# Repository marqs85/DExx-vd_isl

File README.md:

DExx-vd_isl
==============

DExx-vd_isl is advanced video digitizer add-on module for a number of Terasic FPGA development boards. It has been initially used as a development board for OSSC Pro scan converter but over time has been tailored towards a standalone product. Please check the [wikipage](https://junkerhq.net/xrgb/index.php?title=DExx-vd_isl) for more information on usage and latest features.

[PCB](pcb/) and firmware of the project are open-source except for certain Intel VIP modules which are planned to be replaced by custom implementations over time. For most parts RTL and SW are derived from OSSC Pro [project](https://github.com/marqs85/ossc_pro/) with only small amount of adaptation code for the supported development boards.

Supported Terasic boards and board specific notes
----------------------------------------------------
* [DE10-Nano](board/de10-nano)
* [C5G](board/c5g)
* [DE2-115](board/de2-115)

Requirements for building and debugging firmware
---------------------------------------------------
* Hardware
  * DExx-vd_isl module and compatible development board

* Software
  * [Altera Quartus Prime + device support files for target FPGA family](http://dl.altera.com/?edition=lite) (v 21.1 or higher - free Lite Edition suffices)
  * Make

Building RTL (bitstream)
--------------------------
1. Load the project (board/\<board\>/\<boardname\>.qpf) in Quartus
2. Generate QSYS output files (only needed before first compilation or when QSYS structure has been modified)
    * Open Platform Designer (Tools -> Platform Designer)
    * Load platform configuration (sys.qsys)
    * Generate output (Generate -> Generate HDL, Generate)
    * Close Platform Designer
3. Build software image if not yet done so that it becomes part of the bitstream (see next section)
4. Generate the FPGA bitstream (Processing -> Start Compilation)
5. Ensure that there are no major timing violations by looking into Timing Analyzer report

NOTE: If the software image (software/sys_controller/mem_init/sys_onchip_memory2_0.hex) was not up to date at the time of compilation, bitstream can be quickly rebuilt with updated hex by running "Processing->Update Memory Initialization File" and "Processing->Start->Start Assembler" in Quartus.

NOTE2: Without Intel VIP license it's only possible to generate a time limited bitstream which needs connection to USB Blaster during use. VIP modules can be excluded by commenting out the "VIP" define from both top-level RTL and sysconfig.h in which case scaler mode is disabled.

Building software image
--------------------------
1. Generate software BSP (first-time only)
~~~~
cd board/<board>/software/sys_controller_bsp
nios2-bsp-generate-files --settings=settings.bsp --bsp-dir=.
~~~~
2. Enter software root directory:
~~~~
cd board/<board>/software/sys_controller
~~~~
3. Build SW for target configuration:
~~~~
make [OPTIONS] [TARGET]
~~~~
OPTIONS may include following definitions:
* APP_CFLAGS_DEFINED_SYMBOLS="-DDEBUG" (debug message are printed to stdout connected to JTAG UART, shown via nios2-terminal)

TARGET is typically one of the following:
* all (Default target. Compiles an ELF file)
* mem_init_generate (Generates a memory initialization file required for bitstream)
* clean (cleans ELF and intermediate files. Should be invoked every time OPTIONS are changed between compilations)

4. Optionally test updated SW by directly downloading memory image to block RAM via JTAG (with DE10-Nano TCK needs to be reduced, see board specific notes)
~~~~
nios2-download sys_controller.elf --go
~~~~

Bitstream deployment
----------------------
Depending on target platform, bitstream can be either stored into serial flash chip or SD card where it is automatically loaded every time FPGA is subsequently powered on.

To program flash on compatible boards, FPGA configuration file must be first converted into JTAG indirect Configuration file (.jic). Open conversion tool ("File->Convert Programming Files") in Quartus, click "Open Conversion Setup Data", select "ossc.cof" and press Generate. Then open Programmer, add generated file (output_files/<filename>.jic) and press Start after which flash is programmed. Installed/updated firmware is activated after power-cycling the board.

See board specific notes for building a SD card image containing the bitstream.

Debugging
------------
1. Rebuild the software in debug mode:
~~~~
make clean && make APP_CFLAGS_DEBUG_LEVEL="-DDEBUG" mem_init_generate
~~~~
2. Download memory image via JTAG and open terminal for UART
~~~~
nios2-download sys_controller.elf --go && nios2-terminal
~~~~
Remember to close nios2-terminal after debug session, otherwise any JTAG transactions will hang/fail.

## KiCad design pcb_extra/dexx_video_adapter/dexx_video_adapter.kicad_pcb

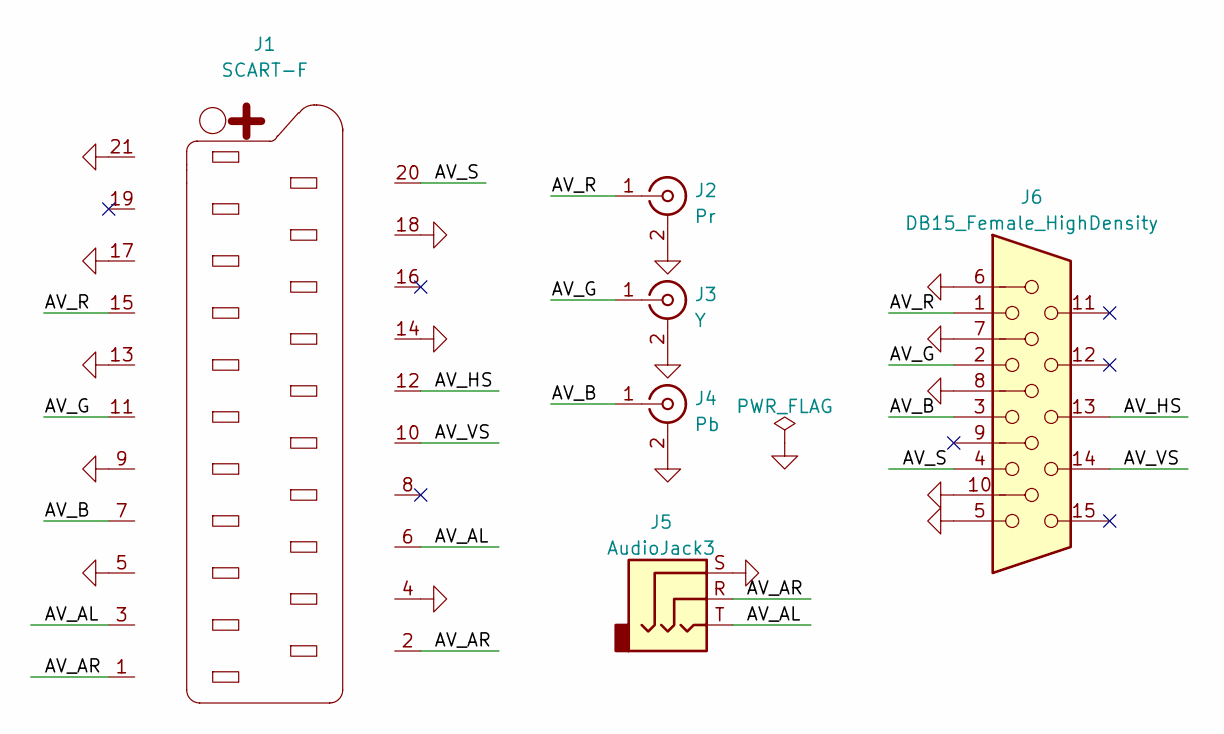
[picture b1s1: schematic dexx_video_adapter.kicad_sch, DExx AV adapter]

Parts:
J1: SCART-F; SCART_CONN
J2: Pr; CUI_RCJ-022
J3: Y; CUI_RCJ-022
J4: Pb; CUI_RCJ-022
J5: AudioJack3; SJ1-3533NG
J6: DB15_Female_HighDensity; VGA_CONN

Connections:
/AV_AL: J1.3, J1.6, J5.T
/AV_AR: J1.1, J1.2, J5.R
/AV_B: J1.7, J4.1 (In), J6.3
/AV_G: J1.11, J3.1 (In), J6.2
/AV_HS: J1.12, J6.13
/AV_R: J1.15, J2.1 (In), J6.1
/AV_S: J1.20, J6.4
/AV_VS: J1.10, J6.14
GND: J1.4, J1.5, J1.9, J1.13, J1.14, J1.17, J1.18, J1.21, J2.2 (Ext), J3.2 (Ext), J4.2 (Ext), J5.S, J6.5, J6.6, J6.7, J6.8, J6.10

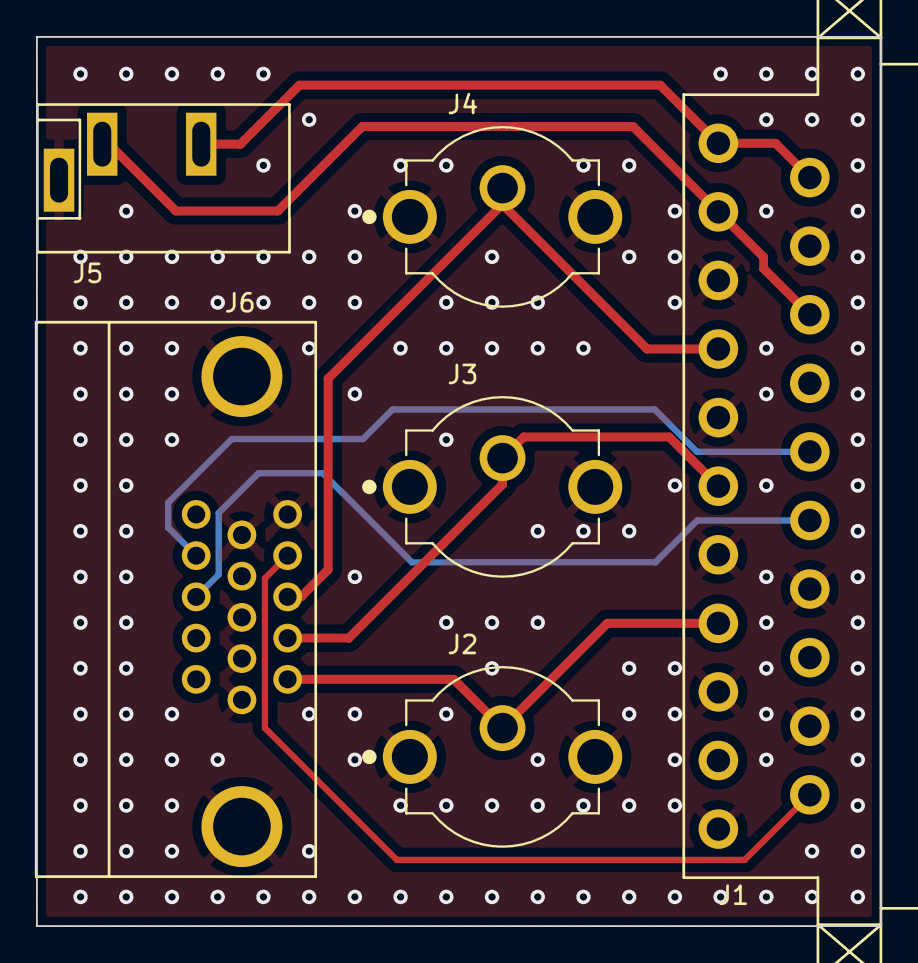
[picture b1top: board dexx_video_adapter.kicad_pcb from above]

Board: 2 copper layers, 46.9 x 49.4 mm, 6 parts (0 on the bottom side), 9 nets.

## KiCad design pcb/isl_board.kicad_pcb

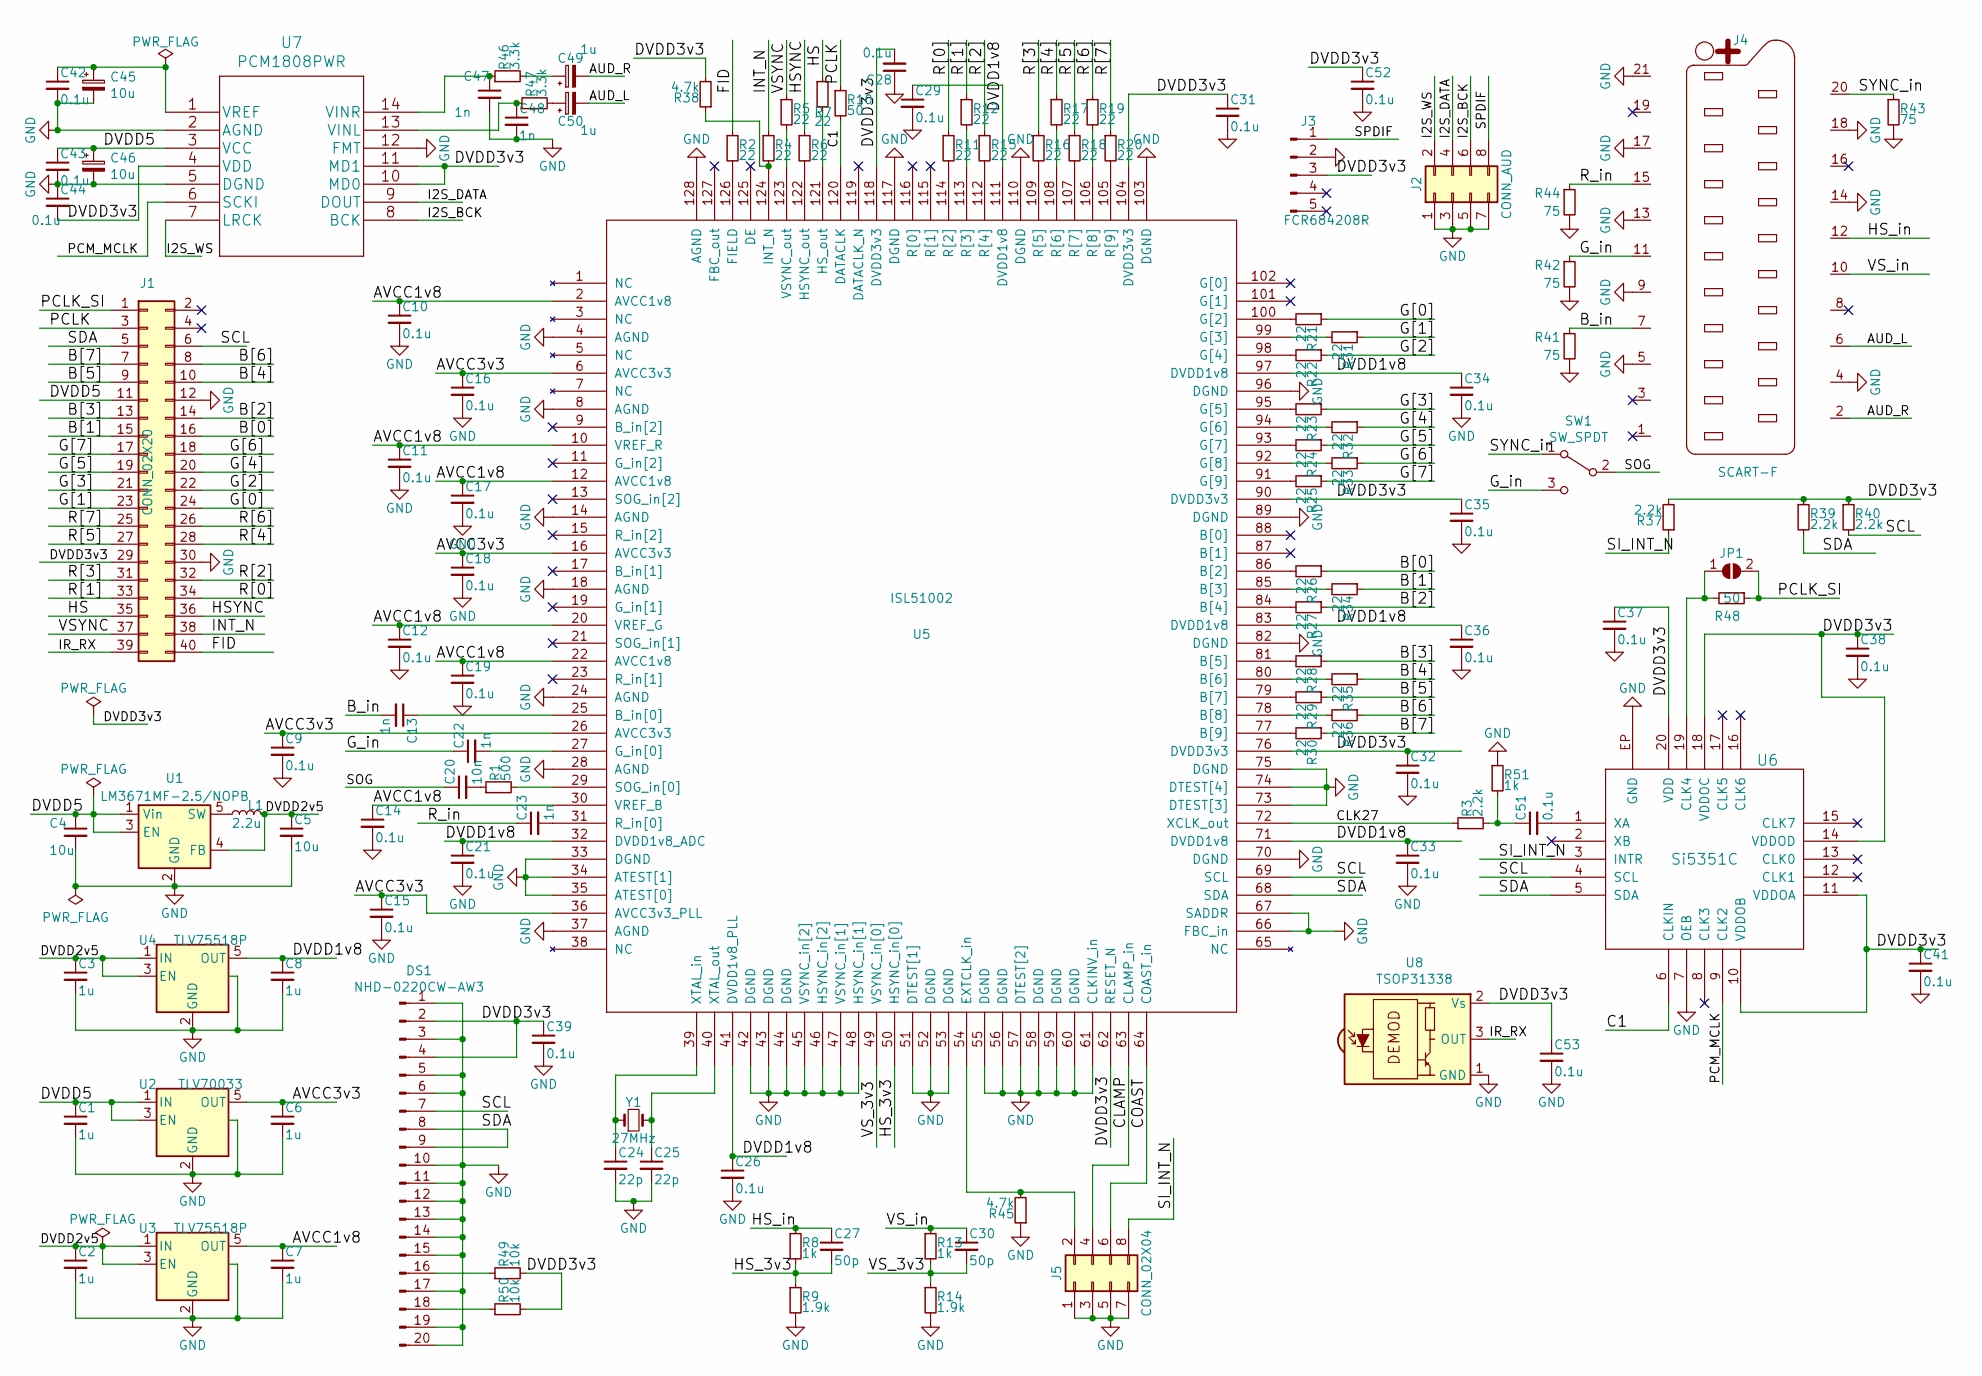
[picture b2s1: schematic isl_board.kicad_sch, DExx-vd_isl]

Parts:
C1, C2, C3, C6, C7, C8: 1u; SM0603_Capa_libcms
C4, C5: 10u; SM0603_Capa_libcms
C9, C10, C11, C12, C14, C15, C16, C17, C18, C19, C21, C26, C28, C29, C31, C32, C33, C34, C35, C36, C37, C38, C39, C41, C42, C43, C44, C51, C52, C53: 0.1u; SM0603_Capa_libcms
C13, C22, C23, C47, C48: 1n; SM0603_Capa_libcms
C20: 10n; SM0603_Capa_libcms
C24, C25: 22p; SM0603_Capa_libcms
C27, C30: 50p; SM0603_Capa_libcms
C45, C46: 10u; SM0805_libcms
C49, C50: 1u; SM0805_libcms
DS1: NHD-0220CW-AW3; PinHeader_1x20_P2.54mm_Vertical
J1: CONN_02X20; Pin_Header_Straight_2x20_Pitch2.54mm
J2: CONN_AUD; PinHeader_2x04_P2.54mm_Vertical
J3: FCR684208R
J4: SCART-F; SCART_CONN
J5: CONN_02X04; PinHeader_2x04_P2.54mm_Vertical
JP1: SolderJumper_2_Open; SolderJumper-2_P1.3mm_Open_Pad1.0x0.75mm
L1: 2.2u; CDRH2D14
R1: 500; SM0603_Resistor_libcms
R2, R4, R5, R6, R7, R11, R12, R15, R16, R17, R18, R19, R20, R21, R22, R23, R24, R25, R26, R27, R28, R29, R30, R31, R32, R33, R34, R35, R36: 22; SM0603_Resistor_libcms
R3, R37, R39, R40: 2.2k; SM0603_Resistor_libcms
R8, R13, R51: 1k; SM0603_Resistor_libcms
R9, R14: 1.9k; SM0603_Resistor_libcms
R10, R48: 50; SM0603_Resistor_libcms
R38, R45: 4.7k; SM0603_Resistor_libcms
R41, R42, R43, R44: 75; SM0603_Resistor_libcms
R46, R47: 3.3k; SM0603_Resistor_libcms
R49, R50: 10k; SM0603_Resistor_libcms
SW1: SW_SPDT; PinHeader_1x03_P2.54mm_Vertical
U1: LM3671MF-2.5/NOPB; SOT-23-5_Handsoldering
U2: TLV70033; SOT-23-5_Handsoldering
U3, U4: TLV75518P; SOT-23-5_Handsoldering
U5: ISL51002; MQFP-128_thermal
U6: Si5351C; QFN-20-1EP_4x4mm_Pitch0.5mm_Handsoldering
U7: PCM1808PWR
U8: TSOP31338; Vishay_CAST-3Pin
Y1: 27MHz; ECS-3X9X

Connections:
/AUD_L: C50.2, J4.6
/AUD_R: C49.2, J4.2
/AVCC1v8: C7.1, C10.1, C11.1, C12.1, C14.1, C17.1, C19.1, U3.5 (OUT), U5.2 (AVCC1v8), U5.10 (VREF_R), U5.12 (AVCC1v8), U5.20 (VREF_G), U5.22 (AVCC1v8), U5.30 (VREF_B)
/AVCC3v3: C6.1, C9.1, C15.1, C16.1, C18.1, U2.5 (OUT), U5.6 (AVCC3v3), U5.16 (AVCC3v3), U5.26 (AVCC3v3), U5.36 (AVCC3v3_PLL)
/B[0]: J1.16, R26.1
/B[1]: J1.15, R34.1
/B[2]: J1.14, R27.1
/B[3]: J1.13, R28.1
/B[4]: J1.10, R35.1
/B[5]: J1.9, R29.1
/B[6]: J1.8, R36.1
/B[7]: J1.7, R30.1
/B_in: C13.2, J4.7, R41.1
/C1: R10.2, U5.120 (DATACLK), U6.6 (CLKIN)
/CLAMP: J5.4, U5.63 (CLAMP_in)
/CLK27: R3.1, U5.72 (XCLK_out)
/COAST: J5.6, U5.64 (COAST_in)
/DVDD1v8: C8.1, C21.1, C26.1, C29.1, C33.1, C34.1, C36.1, U4.5 (OUT), U5.32 (DVDD1v8_ADC), U5.41 (DVDD1v8_PLL), U5.71 (DVDD1v8), U5.83 (DVDD1v8), U5.97 (DVDD1v8), U5.111 (DVDD1v8)
/DVDD2v5: C2.1, C3.1, C5.1, L1.2, U1.4 (FB), U3.1 (IN), U3.3 (EN), U4.1 (IN), U4.3 (EN)
/DVDD3v3: C28.2, C31.1, C32.1, C35.1, C37.1, C38.1, C39.1, C41.1, C44.2, C52.1, C53.1, DS1.2, DS1.4, J1.29, J3.3, R37.2, R38.2, R39.1, R40.1, R49.2, R50.2, U5.62 (RESET_N), U5.76 (DVDD3v3), U5.90 (DVDD3v3), U5.104 (DVDD3v3), U5.118 (DVDD3v3), U6.10 (VDDOB), U6.11 (VDDOA), U6.14 (VDDOD), U6.18 (VDDOC), U6.20 (VDD), U7.4 (VDD), U7.10 (MD0), U7.11 (MD1), U8.2 (Vs)
/DVDD5: C1.1, C4.1, C43.1, C46.1, J1.11, U1.1 (Vin), U1.3 (EN), U2.1 (IN), U2.3 (EN), U7.3 (VCC)
/FID: J1.40, R2.1
/G[0]: J1.24, R21.1
/G[1]: J1.23, R31.1
/G[2]: J1.22, R22.1
/G[3]: J1.21, R23.1
/G[4]: J1.20, R32.1
/G[5]: J1.19, R24.1
/G[6]: J1.18, R33.1
/G[7]: J1.17, R25.1
/G_in: C22.1, J4.11, R42.1, SW1.3 (C)
/HS: J1.35, R7.1
/HSYNC: J1.36, R6.1
/HS_3v3: C27.2, R8.2, R9.1, U5.50 (HSYNC_in[0])
/HS_in: C27.1, J4.12, R8.1
/I2S_BCK: J2.6, U7.8 (BCK)
/I2S_DATA: J2.4, U7.9 (DOUT)
/I2S_WS: J2.2, U7.7 (LRCK)
/INT_N: J1.38, R4.1
/IR_RX: J1.39, U8.3 (OUT)
/PCLK: J1.3, R10.1
/PCLK_SI: J1.1, JP1.2 (B), R48.1
/PCM_MCLK: U6.9 (CLK2), U7.6 (SCKI)
/R[0]: J1.34, R11.1
/R[1]: J1.33, R12.1
/R[2]: J1.32, R15.1
/R[3]: J1.31, R16.1
/R[4]: J1.28, R17.1
/R[5]: J1.27, R18.1
/R[6]: J1.26, R19.1
/R[7]: J1.25, R20.1
/R_in: C23.1, J4.15, R44.1
/SCL: DS1.7, J1.6, R40.2, U5.69 (SCL), U6.4 (SCL)
/SDA: DS1.8, DS1.9, J1.5, R39.2, U5.68 (SDA), U6.5 (SDA)
/SI_INT_N: J5.8, R37.1, U6.3 (INTR)
/SOG: C20.1, SW1.2 (B)
/SPDIF: J2.8, J3.1
/SYNC_in: J4.20, R43.1, SW1.1 (A)
/VSYNC: J1.37, R5.1
/VS_3v3: C30.2, R13.2, R14.1, U5.49 (VSYNC_in[0])
/VS_in: C30.1, J4.10, R13.1
GND: C1.2, C2.2, C3.2, C4.2, C5.2, C6.2, C7.2, C8.2, C9.2, C10.2, C11.2, C12.2, C14.2, C15.2, C16.2, C17.2, C18.2, C19.2, C21.2, C24.2, C25.2, C26.2, C28.1, C29.2, C31.2, C32.2, C33.2, C34.2, C35.2, C36.2, C37.2, C38.2, C39.2, C41.2, C42.2, C43.2, C44.1, C45.2, C46.2, C47.2, C48.2, C52.2, C53.2, DS1.1, DS1.3, DS1.5, DS1.6, DS1.10, DS1.11, DS1.12, DS1.13, DS1.14, DS1.15, DS1.17, DS1.19, DS1.20, J1.12, J1.30, J2.1, J2.3, J2.5, J2.7, J3.2, J4.4, J4.5, J4.9, J4.13, J4.14, J4.17, J4.18, J4.21, J5.1, J5.3, J5.5, J5.7, R9.2, R14.2, R41.2, R42.2, R43.2, R44.2, R45.1, R51.1, U1.2 (GND), U2.2 (GND), U2.4 (NC), U3.2 (GND), U3.4 (NC), U4.2 (GND), U4.4 (NC), U5.4 (AGND), U5.8 (AGND), U5.14 (AGND), U5.18 (AGND), U5.24 (AGND), U5.28 (AGND), U5.33 (DGND), U5.34 (ATEST[1]), U5.35 (ATEST[0]), U5.37 (AGND), U5.42 (DGND), U5.43 (DGND), U5.44 (DGND), U5.45 (VSYNC_in[2]), U5.46 (HSYNC_in[2]), U5.47 (VSYNC_in[1]), U5.48 (HSYNC_in[1]), U5.51 (DTEST[1]), U5.52 (DGND), U5.53 (DGND), U5.55 (DGND), U5.56 (DGND), U5.57 (DTEST[2]), U5.58 (DGND), U5.59 (DGND), U5.60 (DGND), U5.61 (CLKINV_in), U5.66 (FBC_in), U5.67 (SADDR), U5.70 (DGND), U5.73 (DTEST[3]), U5.74 (DTEST[4]), U5.75 (DGND), U5.82 (DGND), U5.89 (DGND), U5.96 (DGND), U5.103 (DGND), U5.110 (DGND), U5.117 (DGND), U5.128 (AGND), U6.7 (OEB), U6.EP (GND), U7.2 (AGND), U7.5 (DGND), U7.12 (FMT), U8.1 (GND)
unnamed: C13.1, U5.25 (B_in[0])
unnamed: C20.2, R1.1
unnamed: C22.2, U5.27 (G_in[0])
unnamed: C23.2, U5.31 (R_in[0])
unnamed: C24.1, U5.39 (XTAL_in), Y1.1
unnamed: C25.1, U5.40 (XTAL_out), Y1.2
unnamed: C42.1, C45.1, U7.1 (VREF)
unnamed: C47.1, R46.1, U7.14 (VINR)
unnamed: C48.1, R47.1, U7.13 (VINL)
unnamed: C49.1, R46.2
unnamed: C50.1, R47.2
unnamed: C51.1, R3.2, R51.2
unnamed: C51.2, U6.1 (XA)
unnamed: DS1.16, R49.1
unnamed: DS1.18, R50.1
unnamed: J5.2, R45.2, U5.54 (EXTCLK_in)
unnamed: JP1.1 (A), R48.2, U6.19 (CLK4)
unnamed: L1.1, U1.5 (SW)
unnamed: R1.2, U5.29 (SOG_in[0])
unnamed: R2.2, U5.126 (FIELD)
unnamed: R5.2, U5.123 (VSYNC_out)
unnamed: R6.2, U5.122 (HSYNC_out)
unnamed: R7.2, U5.121 (HS_out)
unnamed: R11.2, U5.114 (R[2])
unnamed: R12.2, U5.113 (R[3])
unnamed: R15.2, U5.112 (R[4])
unnamed: R16.2, U5.109 (R[5])
unnamed: R17.2, U5.108 (R[6])
unnamed: R18.2, U5.107 (R[7])
unnamed: R19.2, U5.106 (R[8])
unnamed: R20.2, U5.105 (R[9])
unnamed: R21.2, U5.100 (G[2])
unnamed: R22.2, U5.98 (G[4])
unnamed: R23.2, U5.95 (G[5])
unnamed: R24.2, U5.93 (G[7])
unnamed: R25.2, U5.91 (G[9])
unnamed: R26.2, U5.86 (B[2])
unnamed: R27.2, U5.84 (B[4])
unnamed: R28.2, U5.81 (B[5])
unnamed: R29.2, U5.79 (B[7])
unnamed: R30.2, U5.77 (B[9])
unnamed: R31.2, U5.99 (G[3])
unnamed: R32.2, U5.94 (G[6])
unnamed: R33.2, U5.92 (G[8])
unnamed: R34.2, U5.85 (B[3])
unnamed: R35.2, U5.80 (B[6])
unnamed: R36.2, U5.78 (B[8])
unnamed: R4.2, R38.1, U5.124 (INT_N)

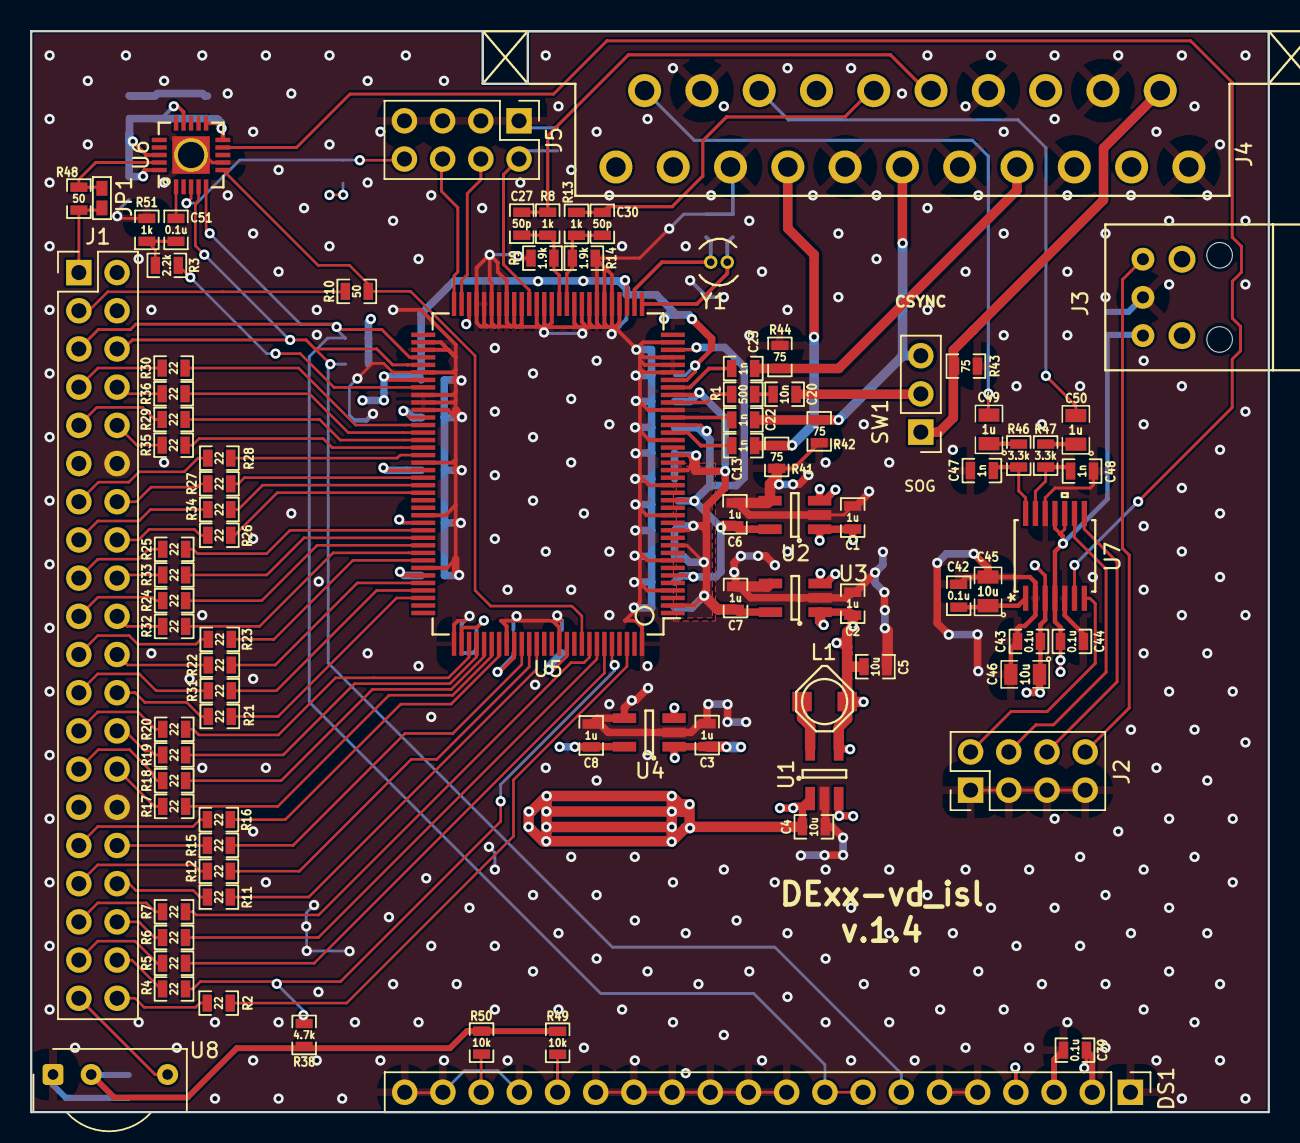
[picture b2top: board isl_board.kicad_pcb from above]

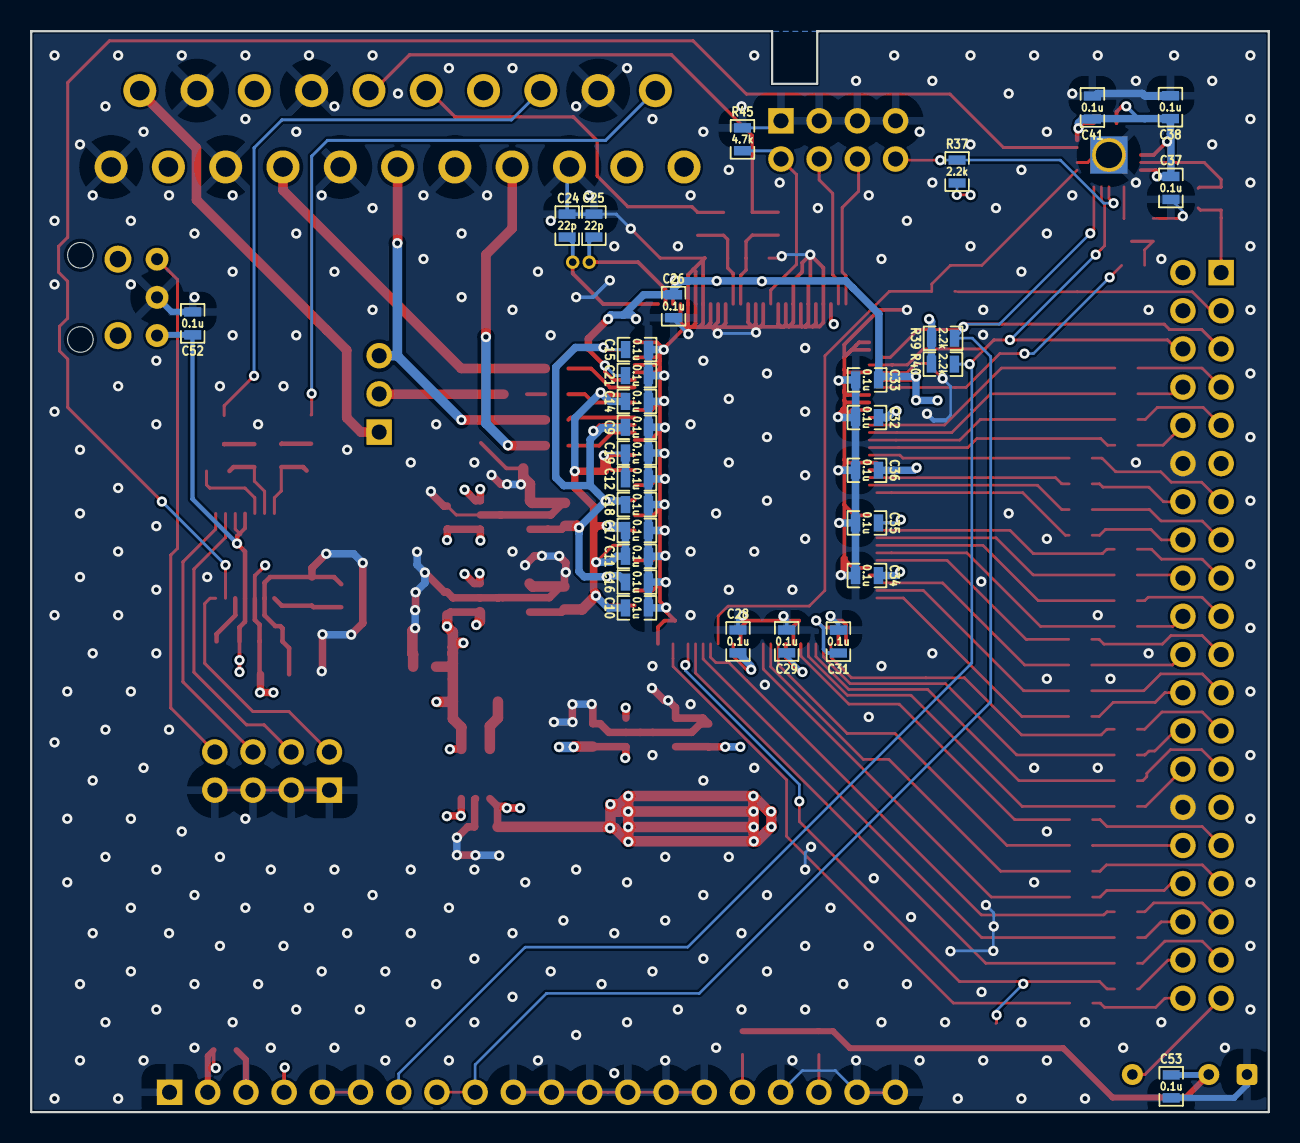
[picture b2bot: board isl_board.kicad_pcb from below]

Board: 4 copper layers, 82.3 x 71.9 mm, 121 parts (31 on the bottom side), 110 nets.

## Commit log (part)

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2018-12-10 add files for original board revision
2020-02-06 add PCB v1.1 gerbers
2020-03-09 update BOM
2020-03-09 add RTL and SW code
2020-03-11 sw: add adaptive LM params for a few 263-line modes
2020-05-01 update project hierarchy
2020-05-07 add new adaptive LM mode configs
2020-05-19 add support for CSC
2020-05-19 add support for DE2-115 dev board
2020-05-19 update de10-nano image
2020-08-30 update code and assignments for v1.3 PCB
2020-11-03 add OSD
2020-11-30 de10-nano: integrate latest updates from ossc_pro
    * new sync processing
    * new mode presets
2020-12-15 add support for flash controller and 48kHz audio
2020-12-22 add option for even field offset adjustment
2021-01-05 update de2-115 fw with initial support for SiI1136
2021-01-13 improve support for sii1136 hdmi tx
2021-01-14 de2-115: add .jic file
2021-02-06 add support for 2560x1440 output
2021-02-06 project port to C5G development board
2021-03-29 integrate updates from ossc_pro project
2021-04-01 Integrate scaler mode test for DE10-Nano
2021-04-06 integrate scaler mode updates
2021-04-06 add .sof bitstream
2021-04-17 scaler mode fixes and VIP performance bump
2021-04-18 Add menu options for 'Visualize Motion Values' and 'Motion Shift' regs (set A) of VIP Dil II
2021-04-19 fix framelock config selection for 2x mode
2021-04-25 simplify framelock configs and add 100/120Hz modes
2021-05-04 sw: allow for VIP Dil II with register set B
2021-05-05 update scaling filter selection
    * enable runtime configuration of PP coeffs
    * enable edge-adaptive mode for SCL
    * add a few extra preset filters
2021-05-18 add ossc_pro as a submodule
    Files common to both projects are now fetched from ossc_pro
    submodule to minimize code duplication. Symlinks are used to hide
    ossc_pro specific hierarchy from DExx-vd_isl design files so that
    they can continue using top-level *_common folders as before.
2021-10-10 integrate updates from ossc_pro fw 0.50
2022-04-03 integrate updates from ossc_pro fw 0.54
2022-04-21 reduce I2C drive strength to minimize interference
2022-05-04 integrate updates from ossc_pro fw 0.55
2022-05-14 integrate updates from ossc_pro fw 0.56
2022-06-20 integrate updates from ossc_pro 0.57
2022-06-30 add README files
2022-07-12 preliminary implementation of profile load/save
    * on DE10-Nano works only when booted via AS
2022-07-20 improve adv7513 video interface timing
    Based on testing with multiple boards, ADV7513 setup and hold times given
    in its Hardware User Guide align with Clock Delay register (0xBA) value
    3 (no delay). This is in conflict with a support forum thread [1] but
    aligns with another thread [2] which implies that listed setup/hold values
    can be adjusted by +/-1.2ns. The change should fix artifacts in 2560x1440_60
    output mode.
2022-07-20 initial implementation of SD save/load profile
    On DE10-Nano MMC block writes are offset by one word maybe due to IO timing
    issue. Bitstream / image files should be generated only after the problem
    has been fixed.
2022-07-28 workaround for MMC block write issue
2022-07-29 firmware release 0.59
    * MMC bwrite issue fixed properly
    * PLLs merged on DE10-Nano version
    * QSYS reset signal routing simplified
    * SD image compressed to reduce repo/download size
2022-08-08 de10-nano: use GPIO1 instead of GPIO0
2022-08-14 de10-nano: update qsf settings for GPIO1
2022-08-29 update de2-115 image
2022-09-10 add dexx_video_adapter pcb design
2022-09-19 integrate updates from ossc_pro fw 0.60
2022-09-24 update fw images
2022-10-04 integrate latest ossc_pro updates
2022-10-22 integrate updates from ossc_pro fw 0.61
2022-11-12 integrate updates from ossc_pro fw 0.62
2023-01-31 integrate updates from ossc_pro fw 0.64
2023-07-12 integrate updates from ossc_pro fw 0.66
2023-08-27 integrate updates from ossc_pro fw 0.67
2024-01-15 integrate updates from ossc_pro fw 0.73

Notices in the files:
parts and their libraries:
Copyright 2016 Accelerated Designs. All rights reserved.
